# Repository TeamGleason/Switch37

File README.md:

# Switch37
Low cost usb switch interface

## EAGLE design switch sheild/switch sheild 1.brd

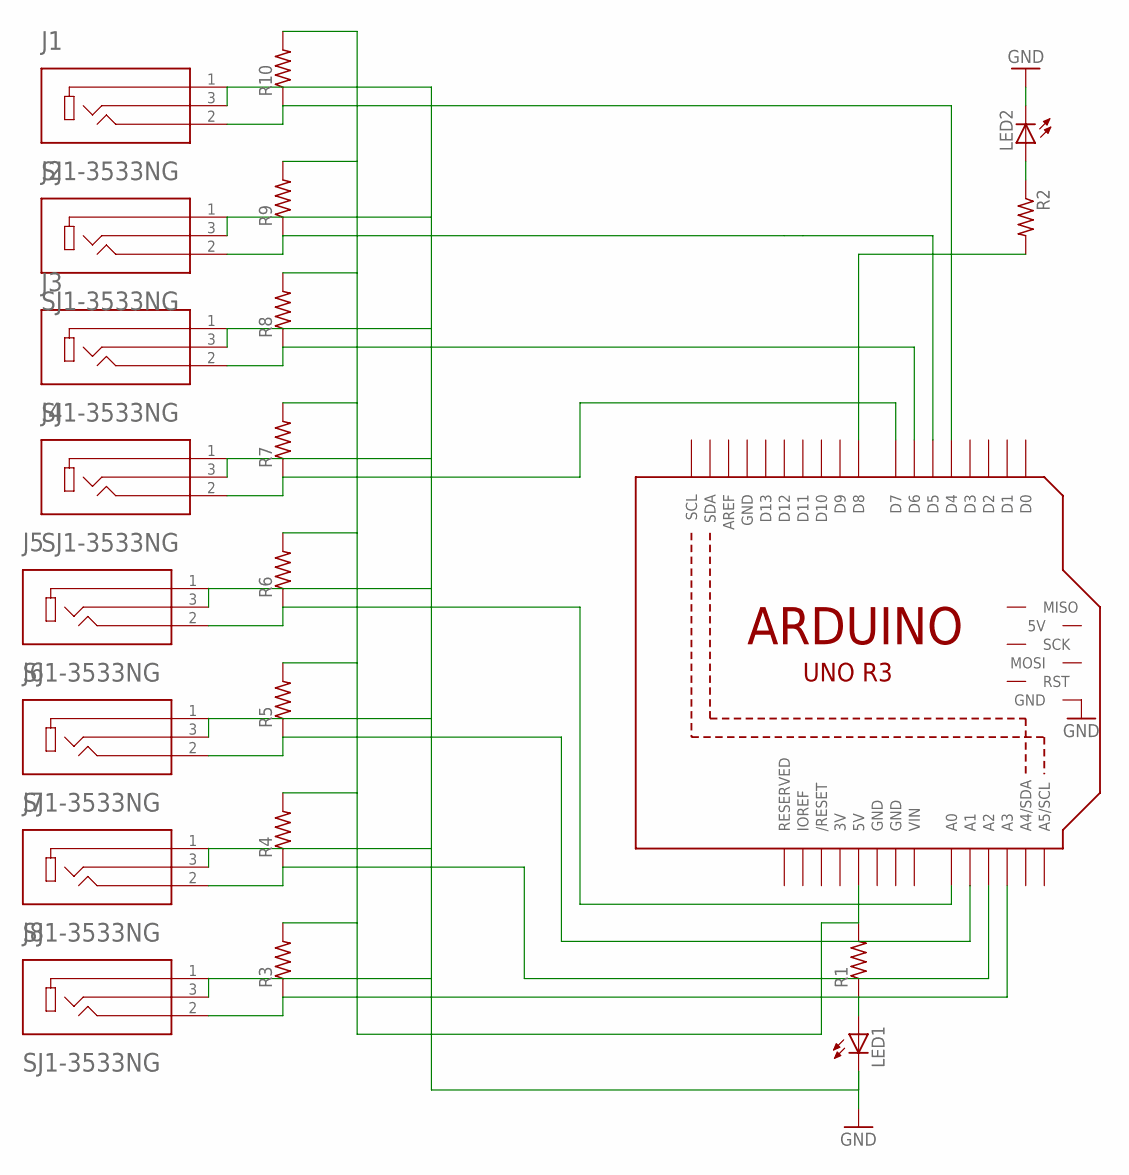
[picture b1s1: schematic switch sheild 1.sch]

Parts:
J1, J2, J3, J4, J5, J6, J7, J8: SJ1-3533NG; CUI_SJ1-3533NG
LED1, LED2: LED3MM
M1: ARDUINO_R3_ICSP; ARDUINOR3_ICSP
R1, R2, R3, R4, R5, R6, R7, R8, R9, R10: R-US_0207/5V; 0207/5V

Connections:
3V: M1.3V
GND: J1.1, J1.3, J2.1, J2.3, J3.1, J3.3, J4.1, J4.3, J5.1, J5.3, J6.1, J6.3, J7.1, J7.3, J8.1, J8.3, LED1.K (C), LED2.K (C), M1.GND, M1.GND@1 (GND), M1.GND@2 (GND), M1.GND@3 (GND)
unnamed: M1.D8, R2.2
unnamed: M1.5V, R1.2, R3.2, R4.2, R5.2, R6.2, R7.2, R8.2, R9.2, R10.2
unnamed: J1.2, M1.D4, R10.1
unnamed: J2.2, M1.D5, R9.1
unnamed: J3.2, M1.D6, R8.1
unnamed: J4.2, M1.D7, R7.1
unnamed: LED1.A, R1.1
unnamed: J5.2, M1.A0, R6.1
unnamed: J6.2, M1.A1, R5.1
unnamed: J7.2, M1.A2, R4.1
unnamed: J8.2, M1.A3, R3.1
unnamed: LED2.A, R2.1
VIN: M1.VIN

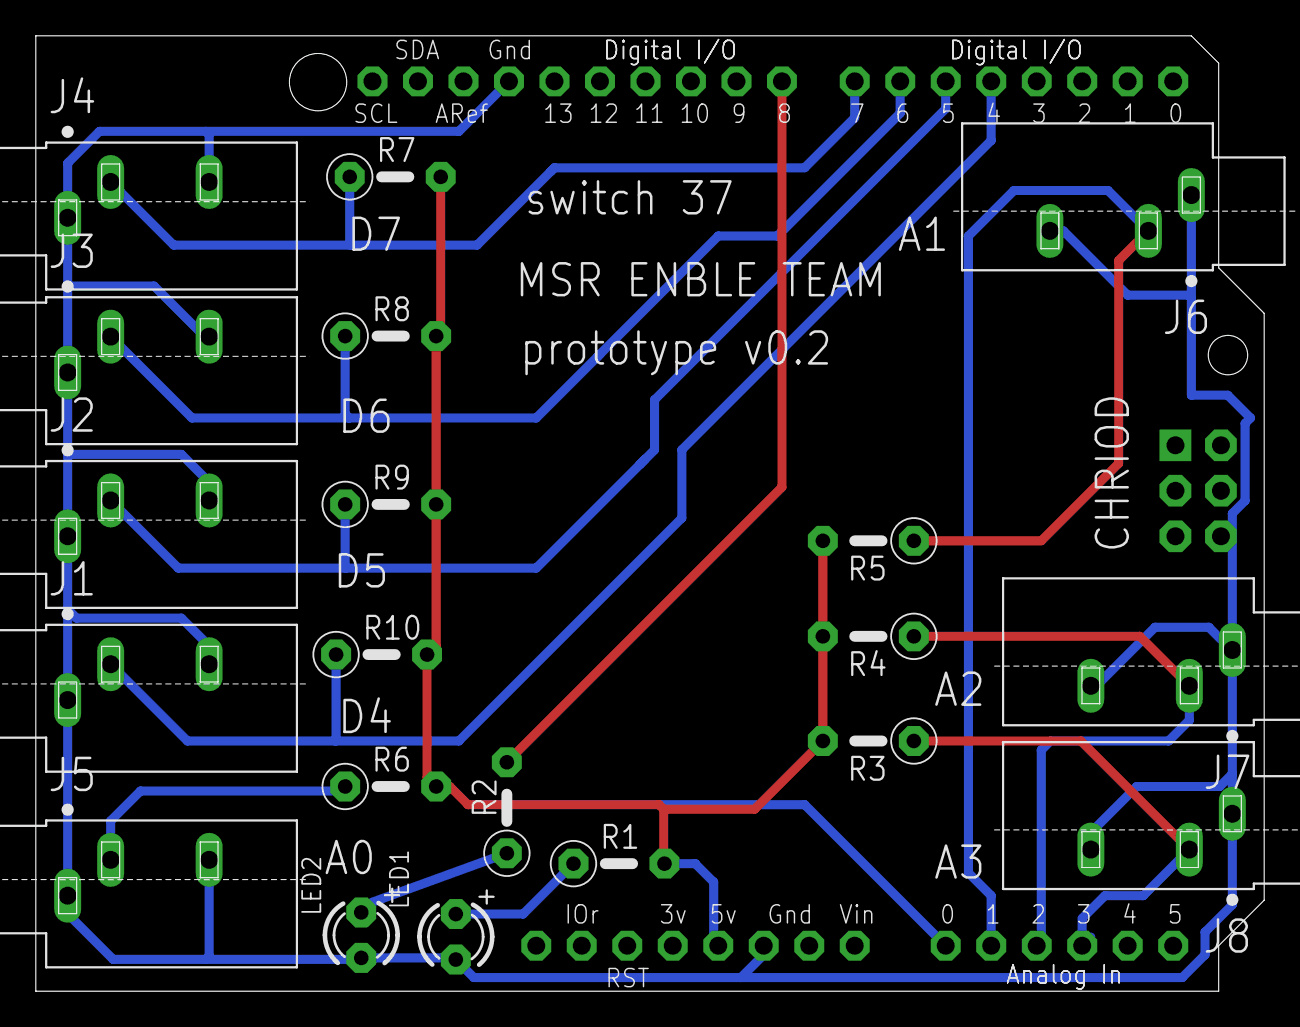
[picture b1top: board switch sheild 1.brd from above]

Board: 2 copper layers, 68.6 x 53.3 mm, 21 parts (0 on the bottom side), 13 nets.

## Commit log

2018-07-30 Initial commit of Arduino code for switch device
2018-08-09 General Updates
    Reduce buttons from 12 to 4
    Change from internal pullup to external pullup resistor setting
    Change to a timer based loop instead of delay
2019-02-15 Add design files for hardware
    -Switch Shield is an arduino shield, tested using a Arduino Leonardo
    -cheap switch is a design which is standalone and arduino compatible
